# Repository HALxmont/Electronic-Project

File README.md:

# Electronic-Project
Disign and implementation a Logarithmic Amplifier

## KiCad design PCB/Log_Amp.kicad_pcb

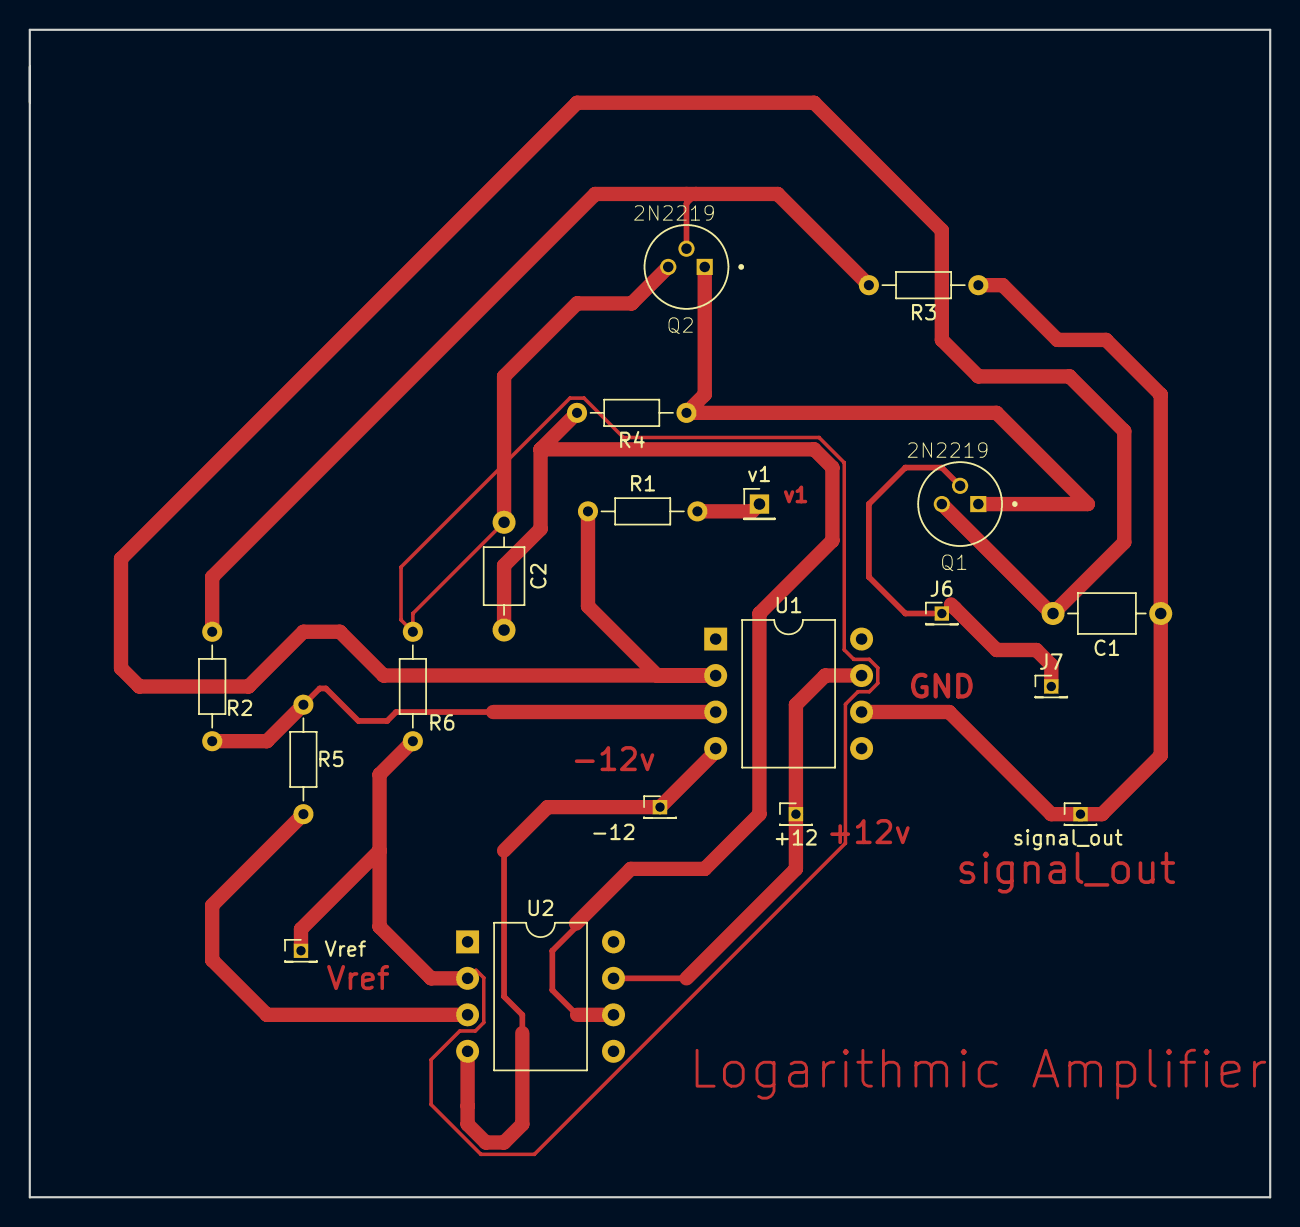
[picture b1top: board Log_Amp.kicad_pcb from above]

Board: 2 copper layers, 86.4 x 81.3 mm, 19 parts (0 on the bottom side), 13 nets.

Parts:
+12: +12; PinHeader_1x01_P1.27mm_Vertical
-12: -12; PinHeader_1x01_P1.27mm_Vertical
C1, C2: 10pF; C_Axial_L3.8mm_D2.6mm_P7.50mm_Horizontal
J6, J7: GND; PinHeader_1x01_P1.27mm_Vertical
Q1, Q2: 2N2219; TO127P584H533-3
R1, R6: 10K; R_Axial_DIN0204_L3.6mm_D1.6mm_P7.62mm_Horizontal
R2: 1K; R_Axial_DIN0204_L3.6mm_D1.6mm_P7.62mm_Horizontal
R3: 15K; R_Axial_DIN0204_L3.6mm_D1.6mm_P7.62mm_Horizontal
R4: 2K; R_Axial_DIN0204_L3.6mm_D1.6mm_P7.62mm_Horizontal
R5: 50K; R_Axial_DIN0204_L3.6mm_D1.6mm_P7.62mm_Horizontal
U1, U2: 741; DIP-8_W10.16mm
Vref: Vref; PinHeader_1x01_P1.27mm_Vertical
signal_out: signal_out; PinHeader_1x01_P1.27mm_Vertical
v1: V1; PinHeader_1x01_P2.00mm_Vertical

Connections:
GND: Q1.2, R2.2, R5.1, U1.3
unnamed: C1.1, R3.1, U1.6, signal_out.1
unnamed: C1.2, Q1.3, R1.1, U1.2
unnamed: C2.1, Q2.3, R6.1, U2.2
unnamed: C2.2, R4.2, U2.6
unnamed: R1.2, v1.1
unnamed: +12.1, U1.7, U2.7
unnamed: -12.1, U1.4, U2.4
unnamed: R6.2, Vref.1
unnamed: J6.1, J7.1
unnamed: Q1.1, Q2.1, R4.1
unnamed: Q2.2, R2.1, R3.2
unnamed: R5.2, U2.3

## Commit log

2018-12-07 First Push
2018-12-31 inform update. PCB dissing added
2018-12-31 Remove old files
2019-01-25 Pdf update
